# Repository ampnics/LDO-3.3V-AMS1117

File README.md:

# ⚡ AMS1117-3.3 V LDO Power Supply Module

A compact and reliable 3.3 V voltage regulator module built around the AMS1117-3.3 V LDO.  
It converts 5 – 12 V DC input into a regulated 3.3 V output, perfect for powering low-voltage microcontrollers, sensors, and logic circuits.

---

## 🔋 Electrical Specifications

| Parameter | Value / Description |
|------------|---------------------|
| Input Voltage (VIN) | 5 V – 12 V DC |
| Output Voltage (VOUT) | 3.3 V DC (regulated) |
| Max Output Current | 800 mA (typical) |
| Dropout Voltage | ≈ 1.1 V @ 800 mA |
| Regulator IC | AMS1117-3.3 V |
| Protection | Input capacitor filtering |

---

## ⚙️ Features
- Simple linear voltage regulator circuit  
- Works from USB 5 V or external DC source  
- On-board input and output filter capacitors  
- Compact 2-layer PCB designed in KiCad 9.0.1  
- Easy to integrate into breadboards or custom projects  

---

Author
Md Ammar Maniyar  

Hardware Design Engineer 

Ampnics

https://www.youtube.com/@ampnics

https://www.ampnics.com

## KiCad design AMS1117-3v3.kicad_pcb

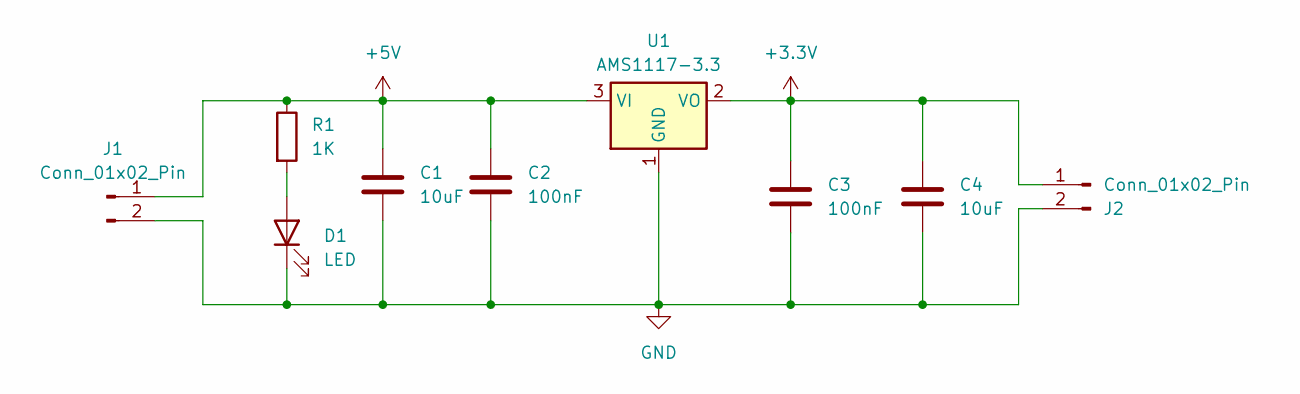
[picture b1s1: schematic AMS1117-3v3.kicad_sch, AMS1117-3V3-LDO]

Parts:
C1, C4: 10uF; C_0603_1608Metric
C2, C3: 100nF; C_0603_1608Metric
D1: LED; LED_0603_1608Metric
J1, J2: Conn_01x02_Pin; PinHeader_1x02_P2.54mm_Vertical
R1: 1K; R_0603_1608Metric
U1: AMS1117-3.3; SOT-223-3_TabPin2

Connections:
+3.3V: C3.1, C4.1, J2.1, U1.2 (VO)
+5V: C1.1, C2.1, J1.1, R1.1, U1.3 (VI)
GND: C1.2, C2.2, C3.2, C4.2, D1.1 (K), J1.2, J2.2, U1.1 (GND)
unnamed: D1.2 (A), R1.2

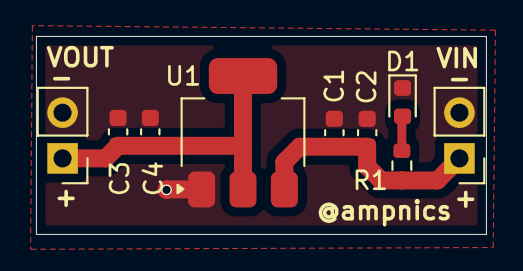
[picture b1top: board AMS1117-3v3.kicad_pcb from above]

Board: 2 copper layers, 25.0 x 11.0 mm, 9 parts (0 on the bottom side), 4 nets.

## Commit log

2025-10-28 Add README for AMS1117-3.3 V LDO Power Supply Module
    Added detailed information about the AMS1117-3.3 V LDO Power Supply Module, including specifications and features.
